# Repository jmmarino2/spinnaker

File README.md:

# spinnaker
Diseño de un pedal de efectos basado en el CI FV-1 de Spin Semiconductor

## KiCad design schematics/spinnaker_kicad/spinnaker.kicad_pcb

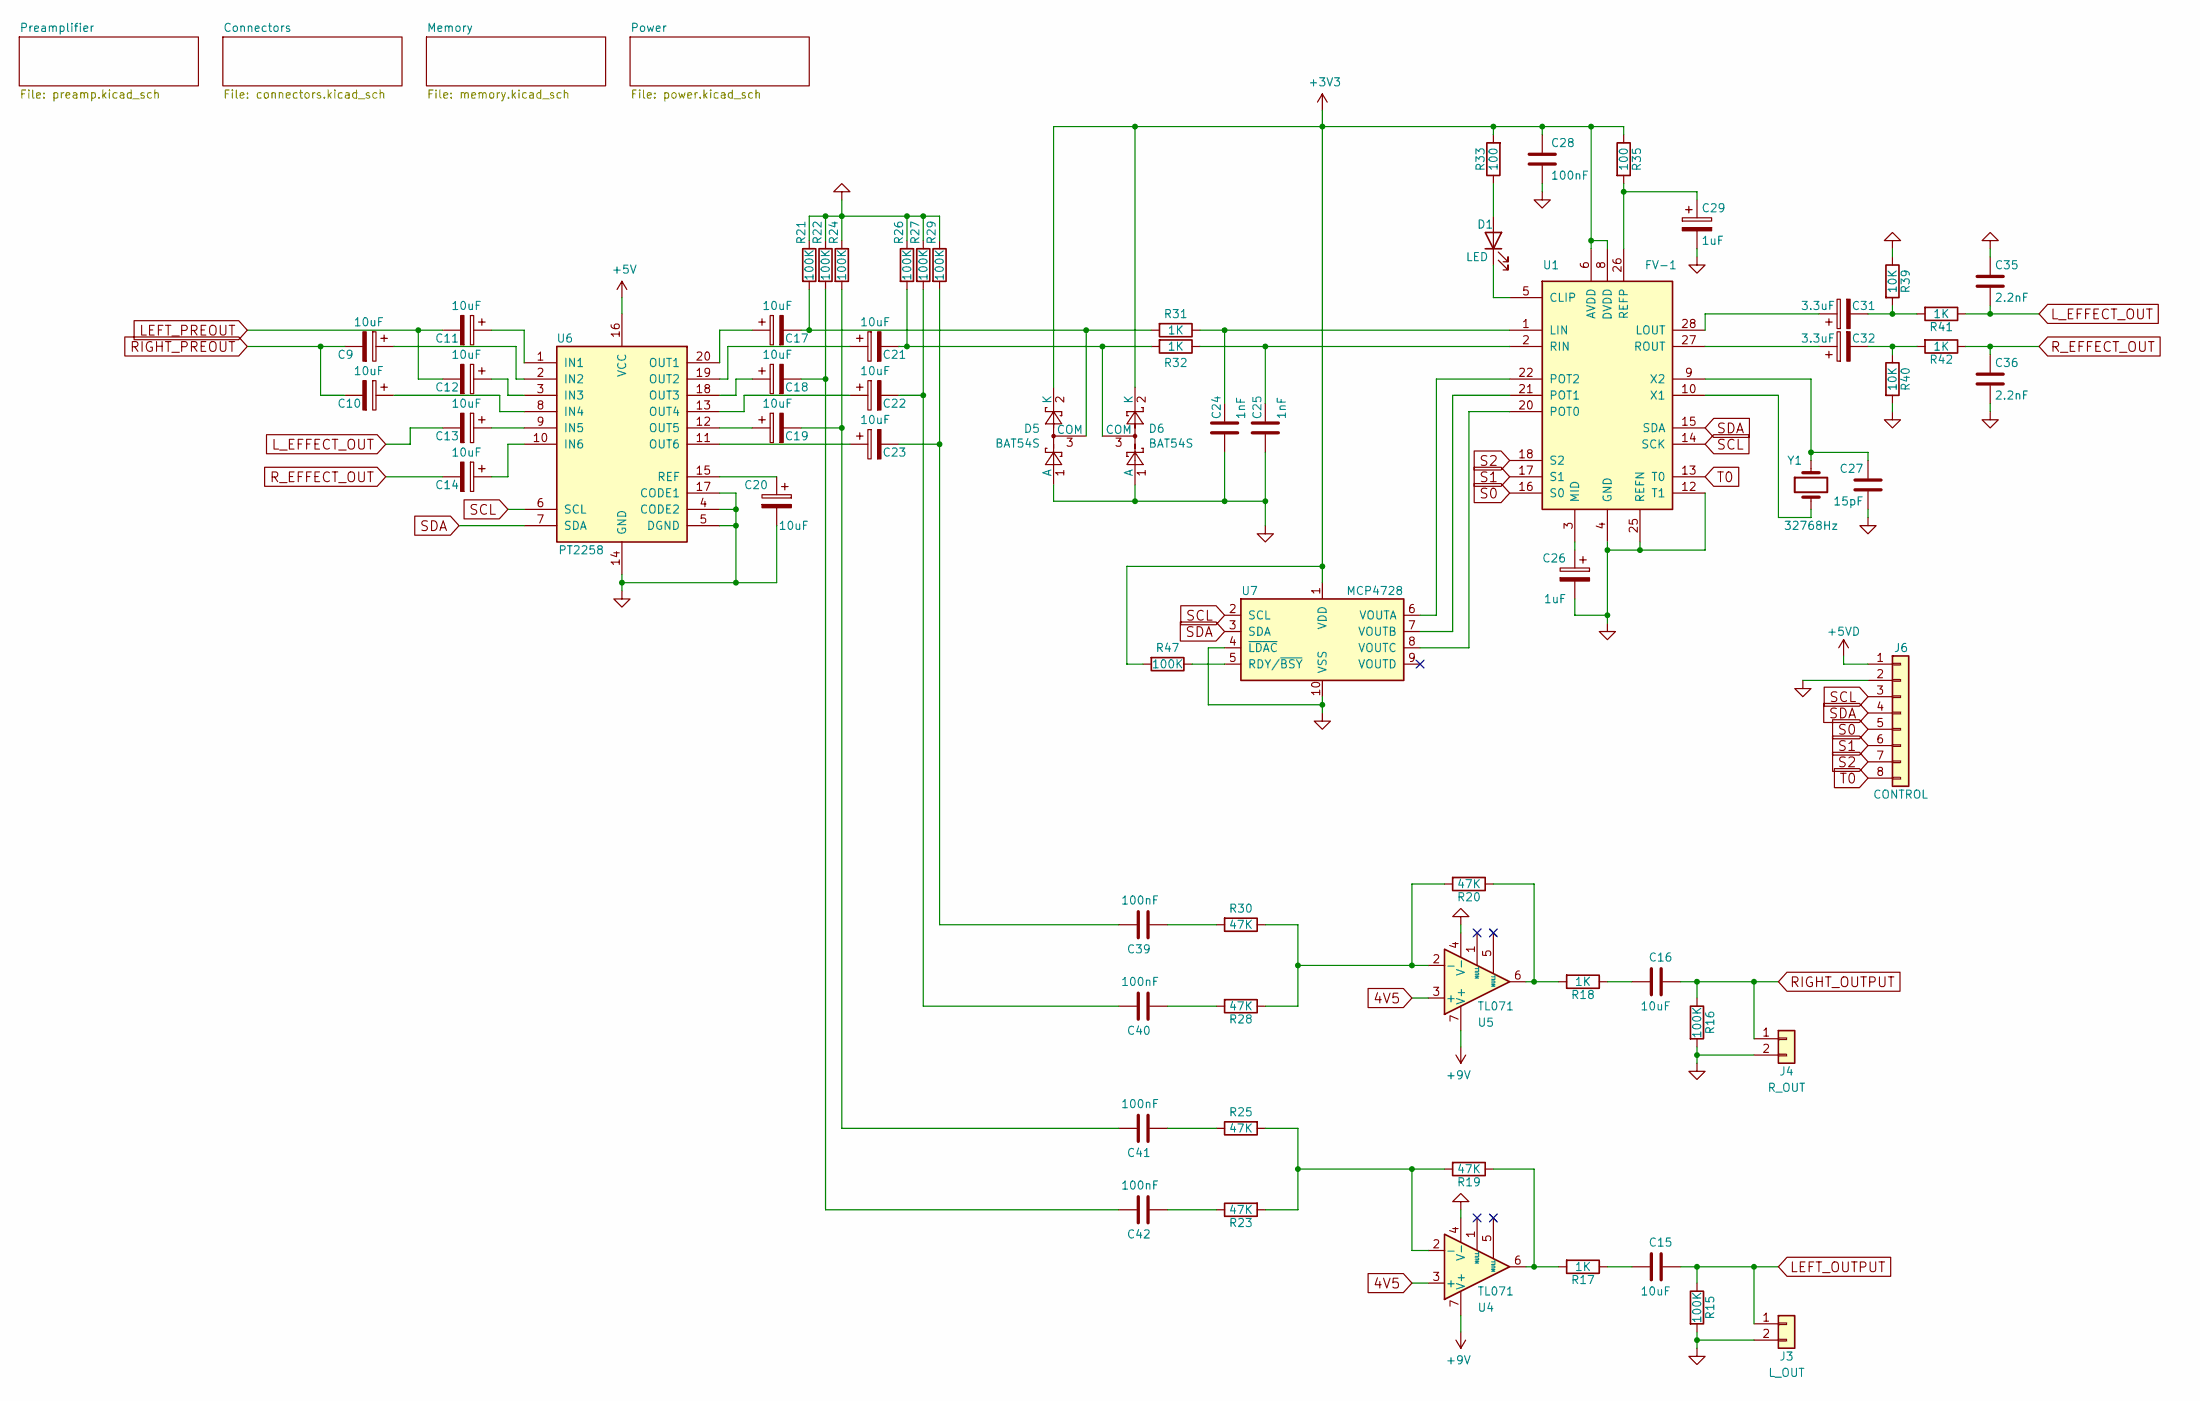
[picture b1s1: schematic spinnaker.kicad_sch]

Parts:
C9, C10, C11, C12, C13, C14, C15, C16, C17, C18, C19, C20, C21, C22, C23: 10uF; C_0805_2012Metric
C24, C25: 1nF; C_0805_2012Metric
C26, C29: 1uF; C_0805_2012Metric
C27: 15pF; C_0805_2012Metric
C28, C39, C40, C41, C42: 100nF; C_0805_2012Metric
C31, C32: 3.3uF; C_0805_2012Metric
C35, C36: 2.2nF; C_0805_2012Metric
D1: LED; SolderWire-0.75sqmm_1x02_P4.8mm_D1.25mm_OD2.3mm
D5, D6: BAT54S; SOT-23
J3: L_OUT; SolderWire-0.75sqmm_1x02_P4.8mm_D1.25mm_OD2.3mm
J4: R_OUT; SolderWire-0.75sqmm_1x02_P4.8mm_D1.25mm_OD2.3mm
J6: CONTROL; JST_PH_B8B-PH-K_1x08_P2.00mm_Vertical
R15, R16, R21, R22, R24, R26, R27, R29, R47: 100K; R_0805_2012Metric
R17, R18, R31, R32, R41, R42: 1K; R_0805_2012Metric
R19, R20, R23, R25, R28, R30: 47K; R_0805_2012Metric
R33, R35: 100; R_0805_2012Metric
R39, R40: 10K; R_0805_2012Metric
U1: FV-1; SOIC-28W_7.5x17.9mm_P1.27mm
U4, U5: TL071; SOIC-8_3.9x4.9mm_P1.27mm
U6: PT2258; SO-20_12.8x7.5mm_P1.27mm
U7: MCP4728; MSOP-10_3x3mm_P0.5mm
Y1: 32768Hz; Crystal_SMD_3215-2Pin_3.2x1.5mm

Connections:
4V5: U4.3 (+), U5.3 (+); also elsewhere on the board
+5V: U6.16 (VCC); also elsewhere on the board
+5VD: J6.1; also elsewhere on the board
+9V: U4.7 (V+), U5.7 (V+); also elsewhere on the board
Earth: C20.2, C24.2, C25.2, C26.2, C27.2, C28.1, C29.2, C35.1, C36.2, D5.1 (A), D6.1 (A), J3.2, J4.2, J6.2, R15.2, R16.2, R21.1, R22.1, R24.1, R26.1, R27.1, R29.1, R39.1, R40.2, U1.4 (GND), U1.7 (GND), U1.11 (GND), U1.12 (T1), U1.19 (GND), U1.24 (GND), U1.25 (REFN), U4.4 (V-), U5.4 (V-), U6.4 (CODE2), U6.5 (DGND), U6.14 (GND), U6.17 (CODE1), U7.4 (~LDAC), U7.10 (VSS); also elsewhere on the board
LEFT_OUTPUT: C15.1, J3.1, R15.1
LEFT_PREOUT: C11.2, C12.2; also elsewhere on the board
L_EFFECT_OUT: C13.2, C35.2, R41.1
unnamed: C9.1, U6.2 (IN2)
unnamed: C10.1, U6.8 (IN4)
unnamed: C11.1, U6.1 (IN1)
unnamed: C12.1, U6.3 (IN3)
unnamed: C13.1, U6.9 (IN5)
unnamed: C14.1, U6.10 (IN6)
unnamed: C15.2, R17.1
unnamed: C16.2, R18.1
unnamed: C17.1, U6.20 (OUT1)
unnamed: C17.2, D5.3 (COM), R21.2, R31.2
unnamed: C18.1, U6.18 (OUT3)
unnamed: C18.2, C42.1, R22.2
unnamed: C19.1, U6.12 (OUT5)
unnamed: C19.2, C41.1, R24.2
unnamed: C20.1, U6.15 (REF)
unnamed: C21.1, U6.19 (OUT2)
unnamed: C21.2, D6.3 (COM), R26.2, R32.2
unnamed: C22.1, U6.13 (OUT4)
unnamed: C22.2, C40.1, R27.2
unnamed: C23.1, U6.11 (OUT6)
unnamed: C23.2, C39.1, R29.2
unnamed: C24.1, R31.1, U1.1 (LIN)
unnamed: C25.1, R32.1, U1.2 (RIN)
unnamed: C26.1, U1.3 (MID)
unnamed: C27.1, U1.9 (X2), Y1.1
unnamed: C29.1, R35.2, U1.26 (REFP)
unnamed: C31.1, U1.28 (LOUT)
unnamed: C31.2, R39.2, R41.2
unnamed: C32.1, U1.27 (ROUT)
unnamed: C32.2, R40.1, R42.2
unnamed: C39.2, R30.2
unnamed: C40.2, R28.2
unnamed: C41.2, R25.1
unnamed: C42.2, R23.1
unnamed: D1.1 (K), U1.5 (CLIP)
unnamed: D1.2 (A), R33.1
unnamed: R17.2, R19.1, U4.6
unnamed: R18.2, R20.1, U5.6
unnamed: R19.2, R23.2, R25.2, U4.2 (-)
unnamed: R20.2, R28.1, R30.1, U5.2 (-)
unnamed: U1.10 (X1), Y1.2
unnamed: U1.20 (POT0), U7.8 (VOUTC)
unnamed: U1.21 (POT1), U7.7 (VOUTB)
unnamed: U1.22 (POT2), U7.6 (VOUTA)
RIGHT_OUTPUT: C16.1, J4.1, R16.1
RIGHT_PREOUT: C9.2, C10.2; also elsewhere on the board
R_EFFECT_OUT: C14.2, C36.1, R42.1
S0: J6.5, U1.16 (S0)
S1: J6.6, U1.17 (S1)
S2: J6.7, U1.18 (S2)
SCL: J6.3, U1.14 (SCK), U6.6 (SCL), U7.2 (SCL); also elsewhere on the board
SDA: J6.4, U1.15 (SDA), U6.7 (SDA), U7.3 (SDA); also elsewhere on the board
T0: J6.8, U1.13 (T0)

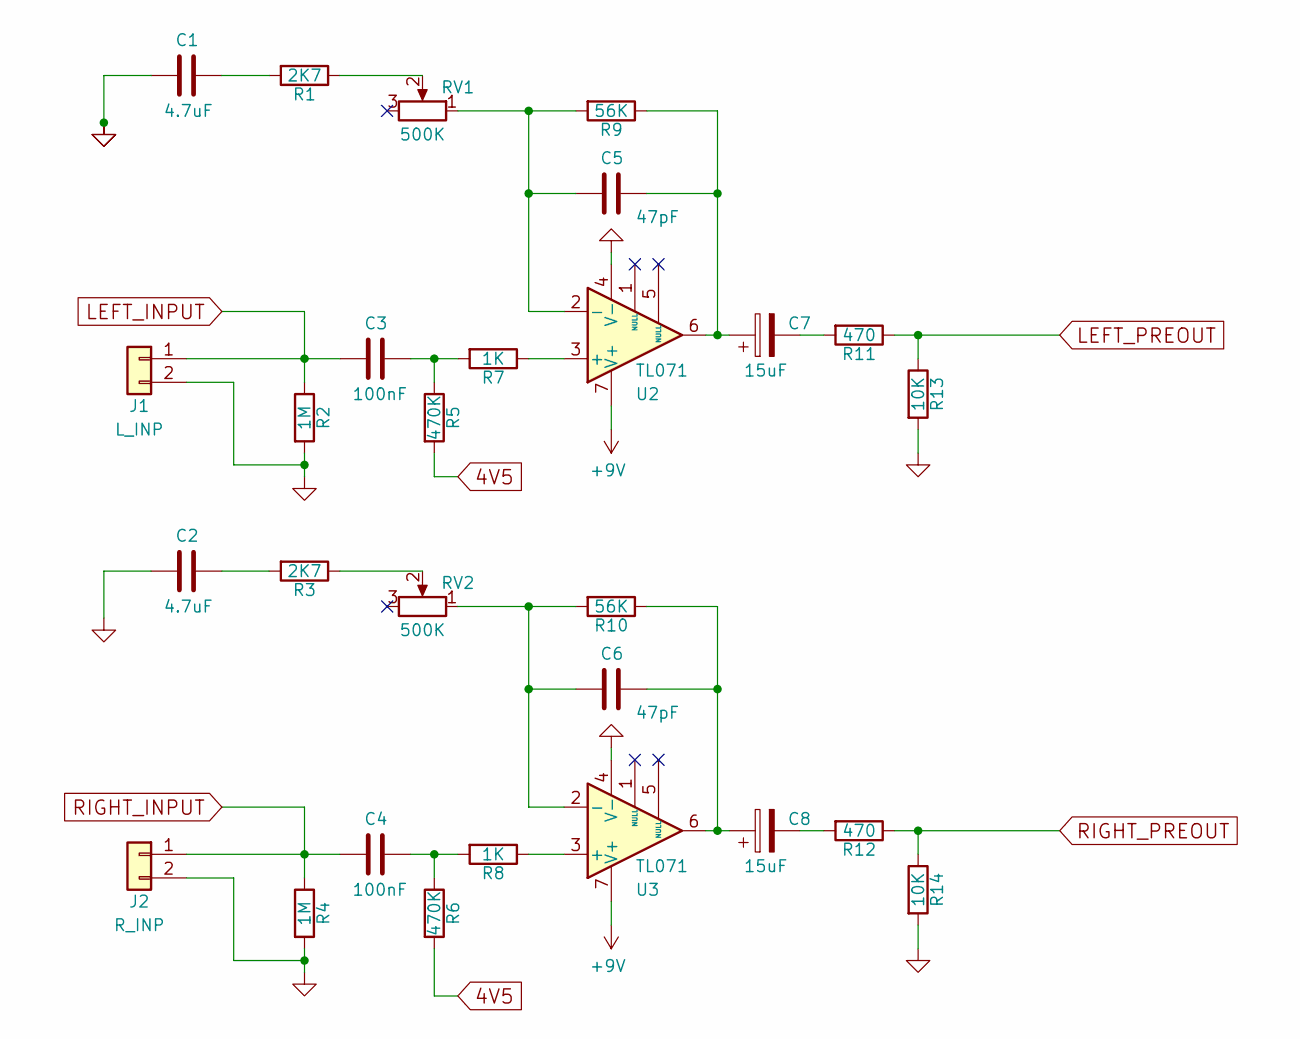
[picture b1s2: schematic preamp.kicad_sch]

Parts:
C1, C2: 4.7uF; C_0805_2012Metric
C3, C4: 100nF; C_0805_2012Metric
C5, C6: 47pF; C_0805_2012Metric
C7, C8: 15uF; C_0805_2012Metric
J1: L_INP; SolderWire-0.75sqmm_1x02_P4.8mm_D1.25mm_OD2.3mm
J2: R_INP; SolderWire-0.75sqmm_1x02_P4.8mm_D1.25mm_OD2.3mm
R1, R3: 2K7; R_0805_2012Metric
R2, R4: 1M; R_0805_2012Metric
R5, R6: 470K; R_0805_2012Metric
R7, R8: 1K; R_0805_2012Metric
R9, R10: 56K; R_0805_2012Metric
R11, R12: 470; R_0805_2012Metric
R13, R14: 10K; R_0805_2012Metric
RV1, RV2: 500K; SolderWire-0.75sqmm_1x02_P4.8mm_D1.25mm_OD2.3mm
U2, U3: TL071; SOIC-8_3.9x4.9mm_P1.27mm

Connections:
4V5: R5.2, R6.2; also elsewhere on the board
+9V: U2.7 (V+), U3.7 (V+); also elsewhere on the board
Earth: C1.2, C2.2, J1.2, J2.2, R2.2, R4.2, R13.2, R14.2, U2.4 (V-), U3.4 (V-); also elsewhere on the board
LEFT_INPUT: C3.2, J1.1, R2.1
LEFT_PREOUT: R11.1, R13.1; also elsewhere on the board
unnamed: C1.1, R1.2
unnamed: C2.1, R3.2
unnamed: C3.1, R5.1, R7.2
unnamed: C4.1, R6.1, R8.2
unnamed: C5.1, C7.1, R9.1, U2.6
unnamed: C5.2, R9.2, RV1.1, U2.2 (-)
unnamed: C6.1, C8.1, R10.1, U3.6
unnamed: C6.2, R10.2, RV2.1, U3.2 (-)
unnamed: C7.2, R11.2
unnamed: C8.2, R12.2
unnamed: R1.1, RV1.2
unnamed: R3.1, RV2.2
unnamed: R7.1, U2.3 (+)
unnamed: R8.1, U3.3 (+)
RIGHT_INPUT: C4.2, J2.1, R4.1
RIGHT_PREOUT: R12.1, R14.1; also elsewhere on the board

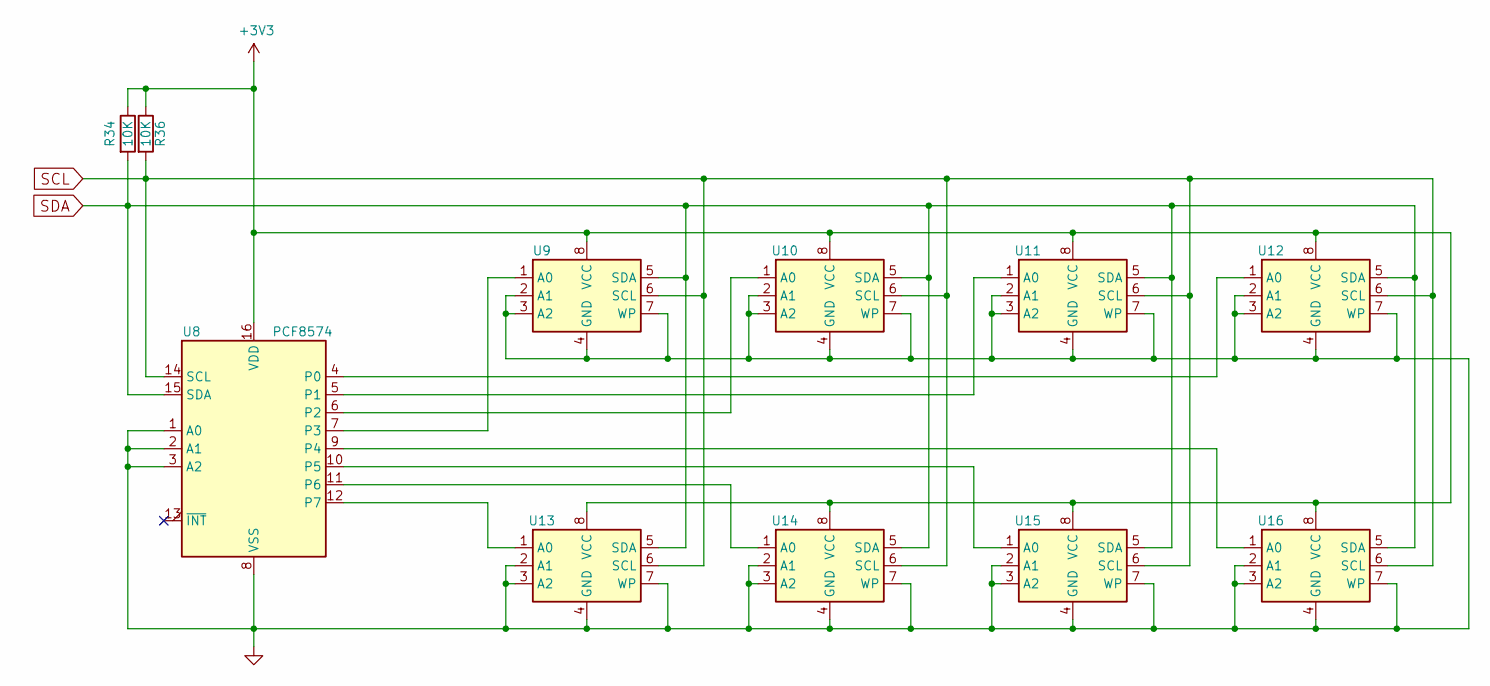
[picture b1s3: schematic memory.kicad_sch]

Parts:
R34, R36: 10K; R_0805_2012Metric
U8: PCF8574; SOIC-16_3.9x9.9mm_P1.27mm
U9, U10, U11, U12, U13, U14, U15, U16: 24LC32; SOIC-8_3.9x4.9mm_P1.27mm

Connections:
Earth: U8.1 (A0), U8.2 (A1), U8.3 (A2), U8.8 (VSS), U9.2 (A1), U9.3 (A2), U9.4 (GND), U9.7 (WP), U10.2 (A1), U10.3 (A2), U10.4 (GND), U10.7 (WP), U11.2 (A1), U11.3 (A2), U11.4 (GND), U11.7 (WP), U12.2 (A1), U12.3 (A2), U12.4 (GND), U12.7 (WP), U13.2 (A1), U13.3 (A2), U13.4 (GND), U13.7 (WP), U14.2 (A1), U14.3 (A2), U14.4 (GND), U14.7 (WP), U15.2 (A1), U15.3 (A2), U15.4 (GND), U15.7 (WP), U16.2 (A1), U16.3 (A2), U16.4 (GND), U16.7 (WP); also elsewhere on the board
unnamed: U8.7 (P3), U9.1 (A0)
unnamed: U8.6 (P2), U10.1 (A0)
unnamed: U8.5 (P1), U11.1 (A0)
unnamed: U8.4 (P0), U12.1 (A0)
unnamed: U8.12 (P7), U13.1 (A0)
unnamed: U8.11 (P6), U14.1 (A0)
unnamed: U8.10 (P5), U15.1 (A0)
unnamed: U8.9 (P4), U16.1 (A0)
SCL: R36.2, U8.14 (SCL), U9.6 (SCL), U10.6 (SCL), U11.6 (SCL), U12.6 (SCL), U13.6 (SCL), U14.6 (SCL), U15.6 (SCL), U16.6 (SCL); also elsewhere on the board
SDA: R34.2, U8.15 (SDA), U9.5 (SDA), U10.5 (SDA), U11.5 (SDA), U12.5 (SDA), U13.5 (SDA), U14.5 (SDA), U15.5 (SDA), U16.5 (SDA); also elsewhere on the board

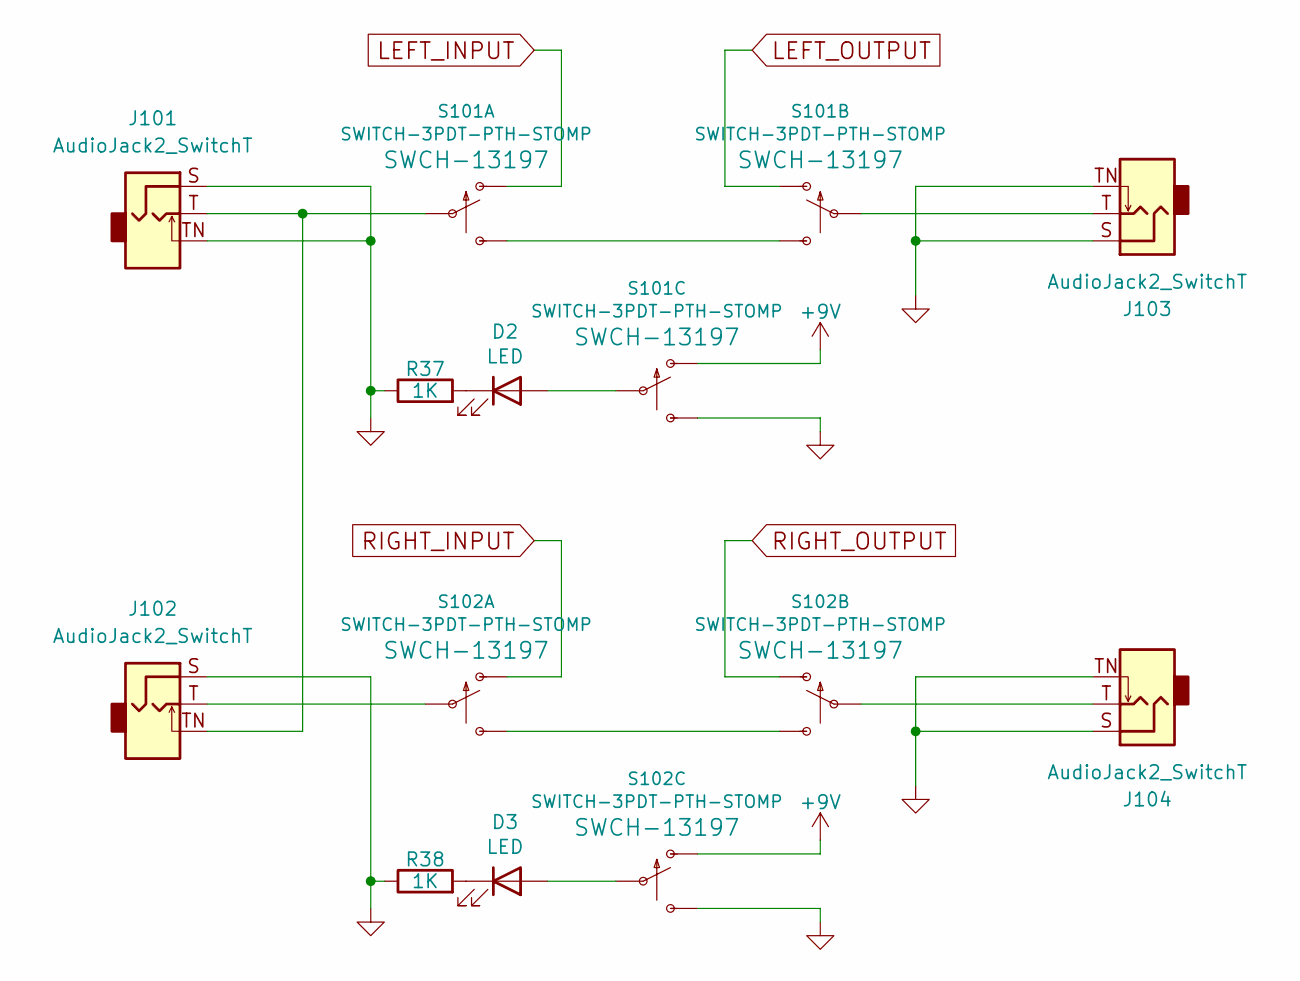
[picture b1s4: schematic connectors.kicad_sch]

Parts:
D2, D3: LED; SolderWire-0.75sqmm_1x02_P4.8mm_D1.25mm_OD2.3mm
J101, J102, J103, J104: AudioJack2_SwitchT
R37, R38: 1K; R_Axial_DIN0204_L3.6mm_D1.6mm_P5.08mm_Horizontal
S101, S102: SWITCH-3PDT-PTH-STOMP; STOMP_SWITCH_3PDT

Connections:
unnamed: D2.1 (K), R37.2
unnamed: D2.2 (A), S101.P$8
unnamed: D3.1 (K), R38.2
unnamed: D3.2 (A), S102.P$8
unnamed: J101.S, J101.TN, J102.S, J103.S, J103.TN, J104.S, J104.TN, R37.1, R38.1, S101.P$9 (S), S102.P$9 (S)
unnamed: J101.T, J102.TN, S101.P$2
unnamed: J102.T, S102.P$2
unnamed: J103.T, S101.P$5
unnamed: J104.T, S102.P$5
unnamed: S101.P$3 (S), S101.P$6 (S)
unnamed: S101.P$7 (O), S102.P$7 (O)
unnamed: S102.P$3 (S), S102.P$6 (S)

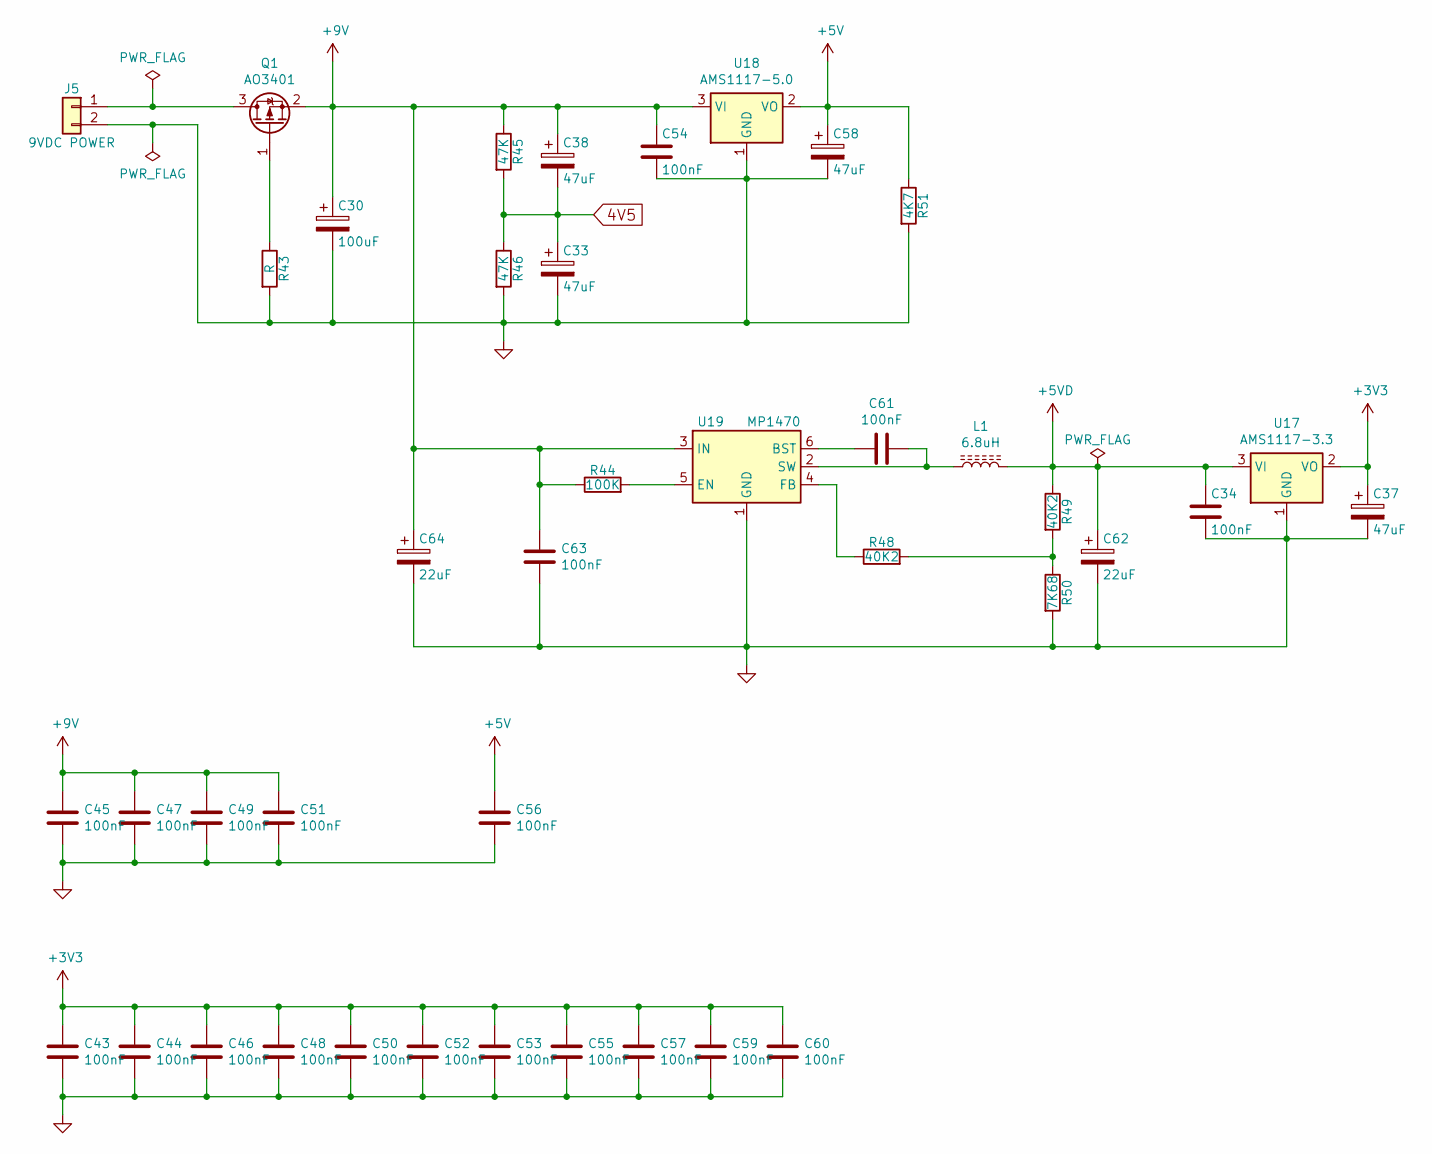
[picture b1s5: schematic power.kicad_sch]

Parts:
C30: 100uF; CP_EIA-7343-31_Kemet-D
C33, C37, C38, C58: 47uF; C_0805_2012Metric
C34, C43, C44, C45, C46, C47, C48, C49, C50, C51, C52, C53, C54, C55, C56, C57, C59, C60, C61, C63: 100nF; C_0805_2012Metric
C62, C64: 22uF; C_0805_2012Metric
J5: 9VDC POWER; JST_PH_B2B-PH-K_1x02_P2.00mm_Vertical
L1: 6.8uH; L_10.4x10.4_H4.8
Q1: AO3401; SOT-23
R43: R; R_0805_2012Metric
R44: 100K; R_0805_2012Metric
R45, R46: 47K; R_0805_2012Metric
R48, R49: 40K2; R_0805_2012Metric
R50: 7K68; R_0805_2012Metric
R51: 4K7; R_0805_2012Metric
U17: AMS1117-3.3; SOT-223-3_TabPin2
U18: AMS1117-5.0; SOT-223-3_TabPin2
U19: MP1470; TSOT-23-6

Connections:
4V5: C33.1, C38.2, R45.2, R46.1; also elsewhere on the board
+5V: C56.1, C58.1, R51.1, U18.2 (VO); also elsewhere on the board
+5VD: C34.1, C62.1, L1.2, R49.1, U17.3 (VI); also elsewhere on the board
+9V: C30.1, C38.1, C45.1, C47.1, C49.1, C51.1, C54.1, C63.1, C64.1, Q1.2 (S), R44.1, R45.1, U18.3 (VI), U19.3 (IN); also elsewhere on the board
Earth: C30.2, C33.2, C34.2, C37.2, C43.2, C44.2, C45.2, C46.2, C47.2, C48.2, C49.2, C50.2, C51.2, C52.2, C53.2, C54.2, C55.2, C56.2, C57.2, C58.2, C59.2, C60.2, C62.2, C63.2, C64.2, J5.2, R43.2, R46.2, R50.2, R51.2, U17.1 (GND), U18.1 (GND), U19.1 (GND); also elsewhere on the board
unnamed: C61.1, U19.6 (BST)
unnamed: C61.2, L1.1, U19.2 (SW)
unnamed: J5.1, Q1.3 (D)
unnamed: Q1.1 (G), R43.1
unnamed: R44.2, U19.5 (EN)
unnamed: R48.1, U19.4 (FB)
unnamed: R48.2, R49.2, R50.1

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
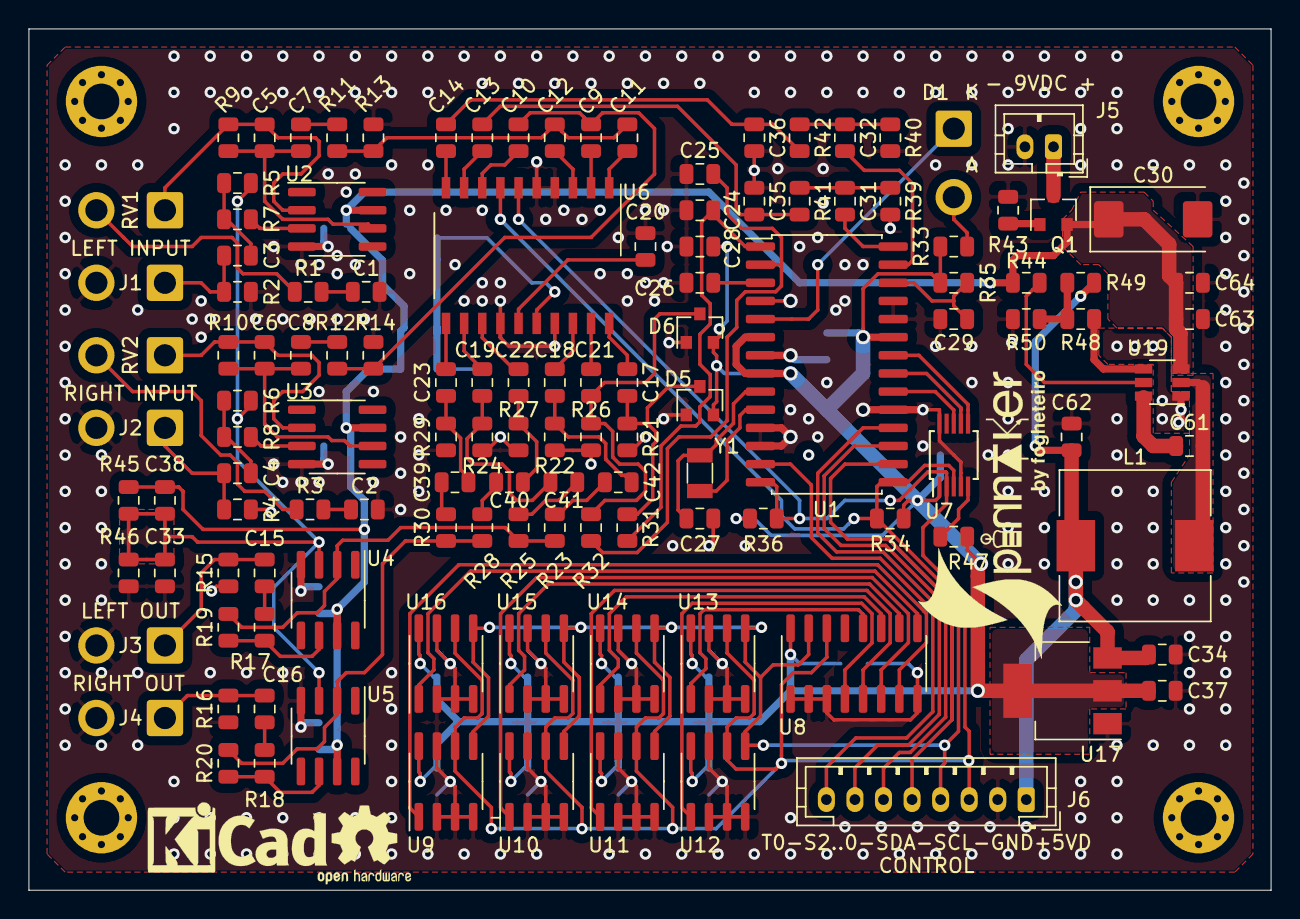
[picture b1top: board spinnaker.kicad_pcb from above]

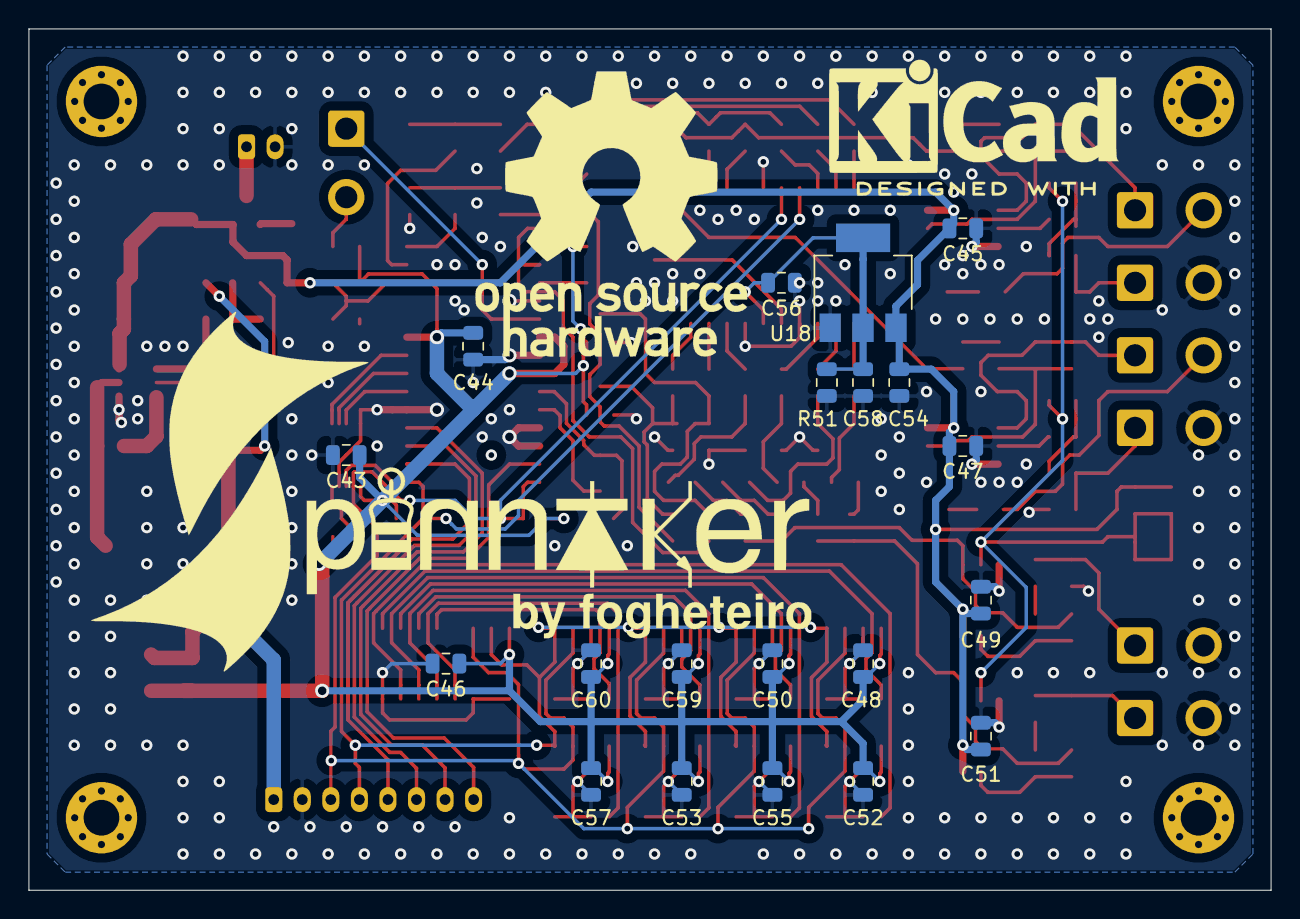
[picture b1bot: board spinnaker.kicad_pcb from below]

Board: 2 copper layers, 87.0 x 60.3 mm, 146 parts (20 on the bottom side), 94 nets.

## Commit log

2018-02-04 Initial load of schematics
2018-08-10 Actualización 10/08/2018
2020-06-17 Actualización de diseño y cambio de versión en Kicad
2020-06-17 Create LICENSE
2020-06-21 Rediseño PCB
2020-06-21 Corrección de conexiones no enrutadas
2020-06-25 Rediseño con SMPS.
2020-06-25 Cambio de conectores a JST-PH. Reducimos alimentación en conector de control a sólo +5VD (SMPS). Otros retoques menores.
2020-06-26 Recolocar etiquetas en silkscreen. Añadir logos en silkscreen. Añadir mallado de vías en planos de tierra.
2020-06-27 Pequeños retoques en la PCB (espaciado de pistas, zona de 3V3 para disipar calor, etc...)
2020-06-28 Se añade logo en silkscreen
2020-06-28 Se añaden librerías de huellas con el logo en diferetes tamaños para el silkscreen
2020-06-30 Eliminación de vias sobre pads. Ligeros retoques en la PCB. Arreglamos el lío de librerías debido al cambio de versión de Kicad.
2020-07-01 Pequeños retoques en zonas de relleno de la PCB y en la silkscreen.
2020-08-10 Gerber files, BOM list
2020-08-11 BOM en html
2020-08-11 Modificado tipo de resistencia R37, R38
2025-03-15 Files upgraded to KICAD_v9.
